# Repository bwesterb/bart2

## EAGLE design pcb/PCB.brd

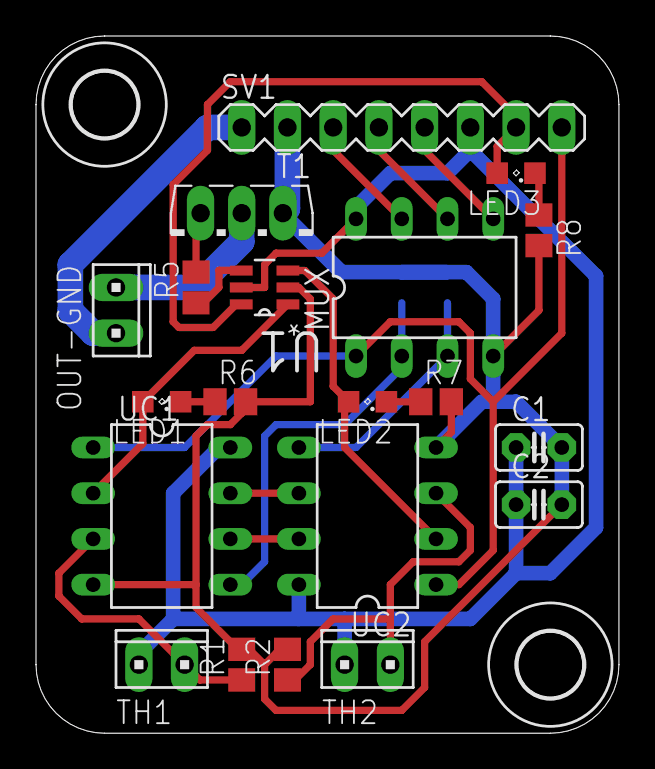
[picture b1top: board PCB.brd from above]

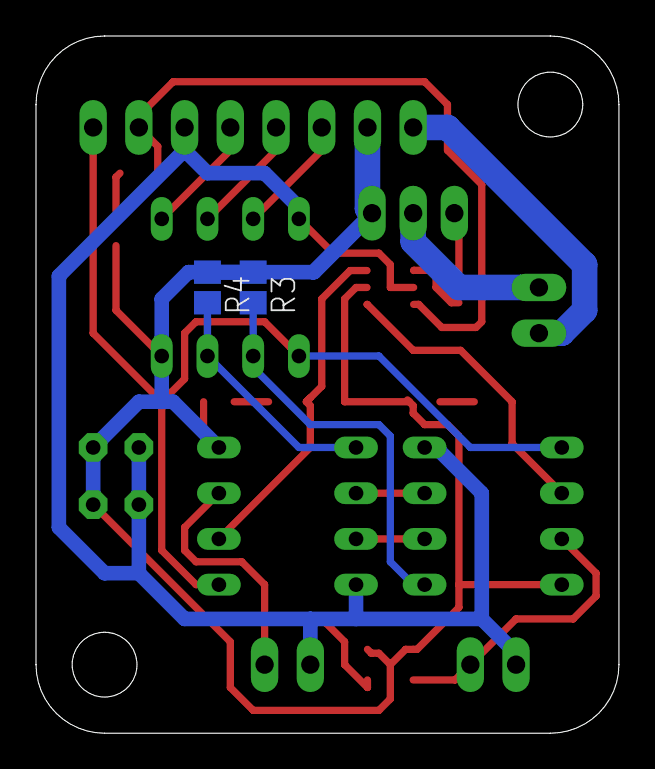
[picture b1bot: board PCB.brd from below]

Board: 2 copper layers, 32.4 x 38.7 mm, 24 parts (2 on the bottom side), 22 nets.

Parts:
C1, C2: C2.5-2
H1, H3: MOUNT-HOLE3.6; 3,6
LED1, LED2, LED3: SML0805
MUX: TINY13-20PU; DIL08
OUT-GND: 10X02MTA
R1, R2: 10k; R0805
R3, R4: 100k; R0805
R5: 1k; R0805
R6, R7, R8: 100; R0805
SV1: MA08-1
T1: TO126V
TH1, TH2: 10X02MTA
U1: SN74LVC1G11DBVR; SOT95P280X145-6N
UC1, UC2: TINY13-20PU; DIL08

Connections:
5V: OUT-GND.1, SV1.1
DRAAD1: MUX.2, R3.2, UC1.5
DRAAD2: MUX.3, R4.2, UC2.5
GND: C1.2, C2.2, MUX.4, R1.2, R2.2, R3.1, R4.1, R6.2, R7.2, R8.2, SV1.2, T1.1, U1.2, UC1.4, UC2.4
HOT: LED3.A, SV1.7, U1.6
MISO: MUX.6, SV1.4
MOSI: MUX.5, SV1.5
unnamed: OUT-GND.2, T1.2
unnamed: LED3.C, R8.1
unnamed: R5.1, U1.4
unnamed: R5.2, T1.3
unnamed: LED2.C, R7.1
unnamed: LED1.C, R6.1
NRST: MUX.1, SV1.8, UC1.1, UC2.1
OUT1: LED1.A, U1.1, UC1.2
OUT2: LED2.A, U1.3, UC2.2
SCLK: MUX.7, SV1.3
THERM1: R1.1, TH1.1, UC1.3
THERM2: R2.1, TH2.1, UC2.3
VCC: C1.1, C2.1, MUX.8, SV1.6, TH1.2, TH2.2, U1.5, UC1.8, UC2.8
WD1: UC1.7, UC2.6
WD2: UC1.6, UC2.7

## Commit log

2016-03-20 rpi: add bootstrap guide
2016-03-20 rpi: stub salt
2016-03-20 programmer (stub)
2016-03-20 vimrc for sls
2016-03-20 blink: use PINB insetad of PORTB
2016-03-22 spitherm: test firmware that measures voltage on pin and sends over SPI
2016-03-22 Adapt blink just to blink LED and left-over pin
    With blink we can measure the frequency of the uC
2016-03-25 draadmaster
2016-03-25 finish draadmaster
2016-03-25 draadslave
2016-03-25 Added pcb
2016-03-25 Added pictures of pcb
2016-03-26 mux: stub
2016-03-28 Complete and fix mux. Decrease size.
2016-03-28 ctrl: initial version
2016-03-29 ctrl: improvements
2016-03-29 PCB image
2016-03-29 add todo
2016-04-03 mux: compensate for the delay it takes to pull the draad down
2016-04-09 avr: add test for AVR timer
2016-04-09 ctrl: fix timer code
2016-04-09 ctrl: compensate for draad pull down time
2016-04-10 avr: add mirror test fw to determine 0 -> 1 voltage
2016-04-16 mux: decode SPI frames
2016-04-16 common: increase DRAAD_DELAY *a lot*
2016-04-16 Split out firmware into ATtiny13 and ATtiny85
2016-04-16 attiny85
2016-04-17 attiny85: SPI test
2016-04-27 rewrite mux for attiny85
2016-04-27 mux: fixing bugs
2016-04-27 mux: fixes
2016-04-30 adds bart2d salt file
2016-04-30 Two more bugs in the mux
2016-04-30 salt: install tig
2016-04-30 mux: another bug
2016-04-30 remove attiny13 implementation of mux
2016-04-30 Update README with new locations of uC firmware
2016-04-30 work on bart2d: spi
2016-04-30 adds SpiConfig struct
2016-05-01 adds .gitignore
2016-05-01 more work on the spi interface
2016-05-01 adds "SpiConfiguredDevice" for convenience
2016-05-06 muxi: Mux Interface
2016-05-08 more work
2016-05-08 more work on bart2d
2016-05-10 Updated pcb
2016-05-17 adds better error messages to OpenSpi
2016-05-17 changes Muxi SPI speedHz to a power of 2 to support RPI mark 1
2016-05-17 rewrite (LSBF)
2016-05-22 unattended upgrades
2016-05-30 ctrl: bounds for 1kOhm resistor
2016-07-03 work on dumper
2016-07-03 removes year, month and day from the time layout
2016-07-03 Install and run bart2d automatically
